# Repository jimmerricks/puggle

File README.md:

# Puggle Keyboard

The Puggle is 5×3+5 keys column-staggered split keyboard based on the [Sofle](https://github.com/josefadamcik/SofleKeyboard) and [Torn](https://github.com/rtitmuss/torn) keyboards. It is currently in development.

- [Keyboard Layout Editor](http://www.keyboard-layout-editor.com/##@_backcolor=%23ffffff&name=Puggle&author=jimmerricks%3B&@_x:2%3B&=E&_x:7%3B&=I%3B&@_y:-0.875&x:1%3B&=W&_x:1%3B&=R&_x:5%3B&=U&_x:1%3B&=O%3B&@_y:-0.875&x:4%3B&=T&_x:3%3B&=Y%3B&@_y:-0.625%3B&=Q&_x:11%3B&=P%3B&@_y:-0.625&x:2%3B&=D&_x:7%3B&=K%3B&@_y:-0.875&x:1%3B&=S&_x:1&n:true%3B&=F&_x:5&n:true%3B&=J&_x:1%3B&=L%3B&@_y:-0.875&x:4%3B&=G&_x:3%3B&=H%3B&@_y:-0.625%3B&=A&_x:11%3B&=%2F:%0A%2F%3B%3B&@_y:-0.625&x:2%3B&=C&_x:7%3B&=%3C%0A,%3B&@_y:-0.875&x:1%3B&=X&_x:1%3B&=V&_x:5%3B&=M&_x:1%3B&=%3E%0A.%3B&@_y:-0.875&x:4%3B&=B&_x:3%3B&=N%3B&@_y:-0.625%3B&=Z&_x:11%3B&=%3F%0A%2F%2F%3B&@_y:-0.5&x:1&a:7%3B&=PgUp%0A%0A%0A%0ALGui&=PgDn%0A%0A%0A%0ALAlt&_x:7%3B&=STab%0A%0A%0A%0ALAlt&=Tab%0A%0A%0A%0ARGui%3B&@_r:13&rx:2.5&ry:8.625&y:-5.5&x:-0.5%3B&=Esc%0A%0A%0A%0ALCtl%3B&@_r:26&y:-1&x:-0.5%3B&=BSpc%3B&@_r:39&y:-1&x:-0.5%3B&=LSft%3B&@_r:-39&rx:10.5&y:-5.5&x:-0.5%3B&=RSft%3B&@_r:-26&y:-1&x:-0.5%3B&=Spc%0A%0A%0A%0AMoves%3B&@_r:-13&y:-1&x:-0.5%3B&=Ent%0A%0A%0A%0ARCtl)

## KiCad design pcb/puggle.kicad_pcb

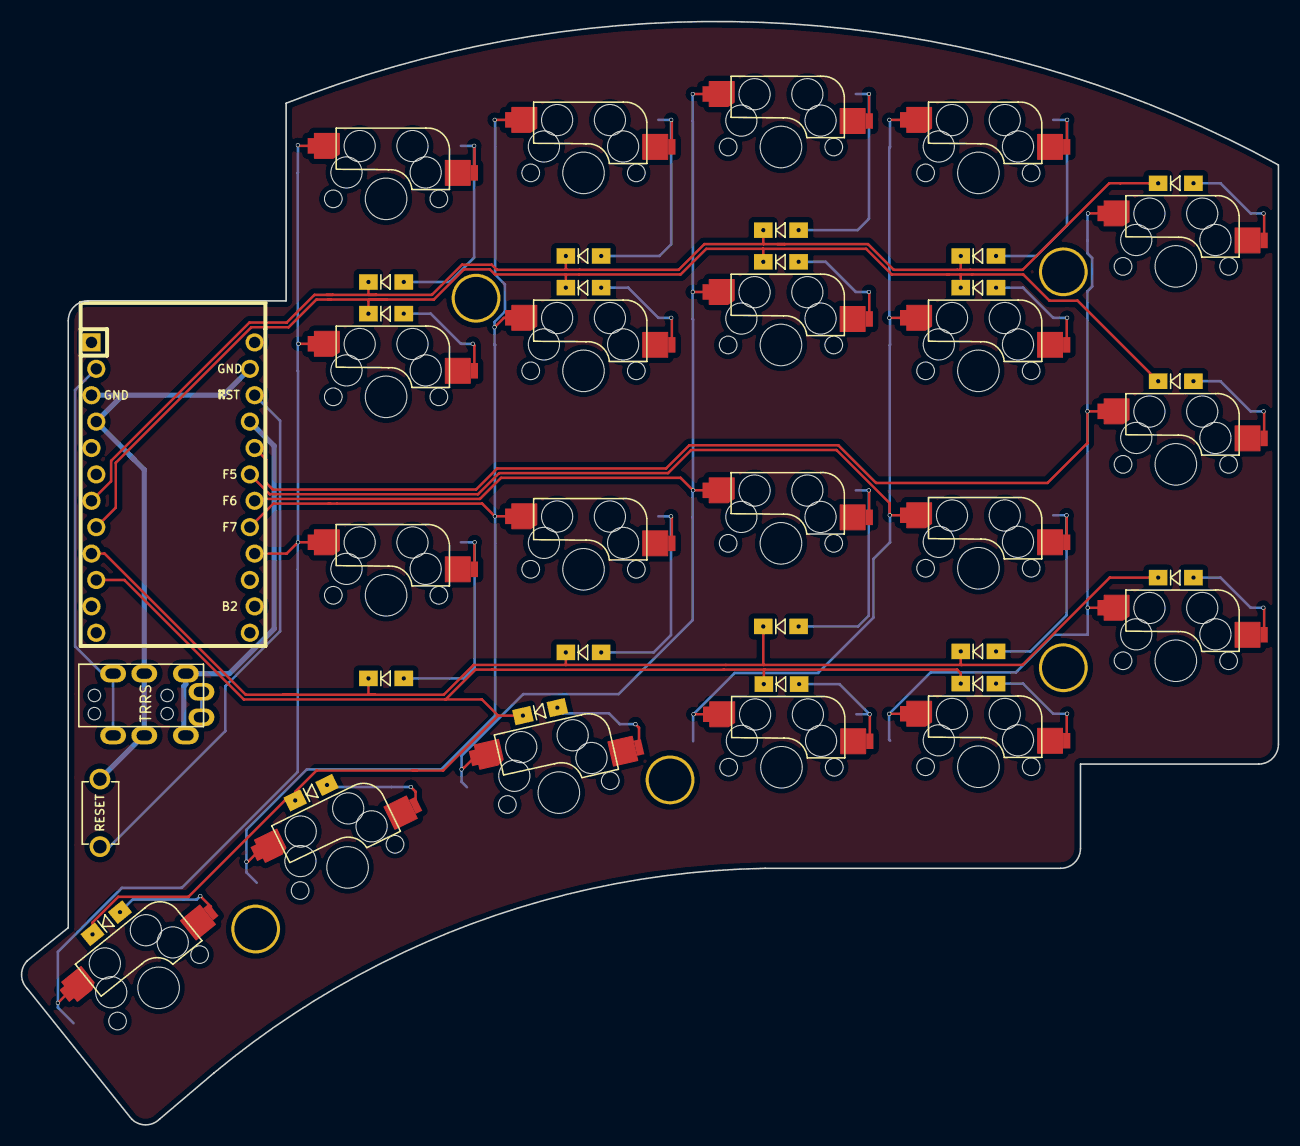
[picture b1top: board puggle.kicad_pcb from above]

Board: 2 copper layers, 121.0 x 106.2 mm, 48 parts (0 on the bottom side), 33 nets.

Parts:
D1, D2, D3, D4, D5, D6, D7, D8, D9, D10, D11, D12, D13, D14, D15, D16, D17, D18, D19, D20: D; Diode_SOD123
J2: 4PIN; MJ-4PP-9
RSW1: SW_RST; TACT_SWITCH_TVBP06
SW1, SW2, SW3, SW4, SW5, SW6, SW7, SW8, SW9, SW10, SW11, SW12, SW13, SW14, SW15, SW16, SW17, SW18, SW19, SW20: SW_PUSH; CherryMX_Hotswap
TH3, TH4, TH5, TH6, TH7: HOLE; HOLE_M2_TH
U1: ProMicro; ArduinoProMicro-ZigZag-DoubleSided

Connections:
DATA: J2.3, U1.2
GND: J2.2, RSW1.1, U1.3, U1.4, U1.23
unnamed: D1.2, SW1.2
unnamed: D2.2, SW2.2
unnamed: D3.2, SW3.2
unnamed: D4.2, SW4.2
unnamed: D5.2, SW5.2
unnamed: D6.2, SW6.2
unnamed: D7.2, SW7.2
unnamed: D8.2, SW8.2
unnamed: D9.2, SW9.2
unnamed: D10.2, SW10.2
unnamed: D11.2, SW11.2
unnamed: D12.2, SW12.2
unnamed: D13.2, SW13.2
unnamed: D14.2, SW14.2
unnamed: D15.2, SW15.2
unnamed: D16.2, SW16.2
unnamed: D17.2, SW17.2
unnamed: D18.2, SW18.2
unnamed: D19.2, SW19.2
unnamed: D20.2, SW20.2
RESET: RSW1.2, U1.22
VCC: J2.1, U1.21
col0: SW5.1, SW10.1, SW15.1, SW20.1, U1.20
col1: SW4.1, SW9.1, SW14.1, SW19.1, U1.19
col2: SW3.1, SW8.1, SW13.1, SW18.1, U1.18
col3: SW2.1, SW7.1, SW12.1, SW17.1, U1.17
col4: SW1.1, SW6.1, SW11.1, SW16.1, U1.16
row0: D1.1, D2.1, D3.1, D4.1, D5.1, U1.7
row1: D6.1, D7.1, D8.1, D9.1, D10.1, U1.8
row2: D11.1, D12.1, D13.1, D14.1, D15.1, U1.9
row3: D16.1, D17.1, D18.1, D19.1, D20.1, U1.10

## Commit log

2020-12-01 Footprints come from the Sofle, https://github.com/josefadamcik/SofleKeyboard.
2020-12-01 Initial commit of Puggle PCB.
2020-12-01 Initial commit of Puggle plates.
2020-12-01 Gerbers added for initial version.
2020-12-01 Simple README and image added.
2020-12-01 Added the MIT licence as per the Sofle.
2020-12-01 Minor changes prior to prototype production.
